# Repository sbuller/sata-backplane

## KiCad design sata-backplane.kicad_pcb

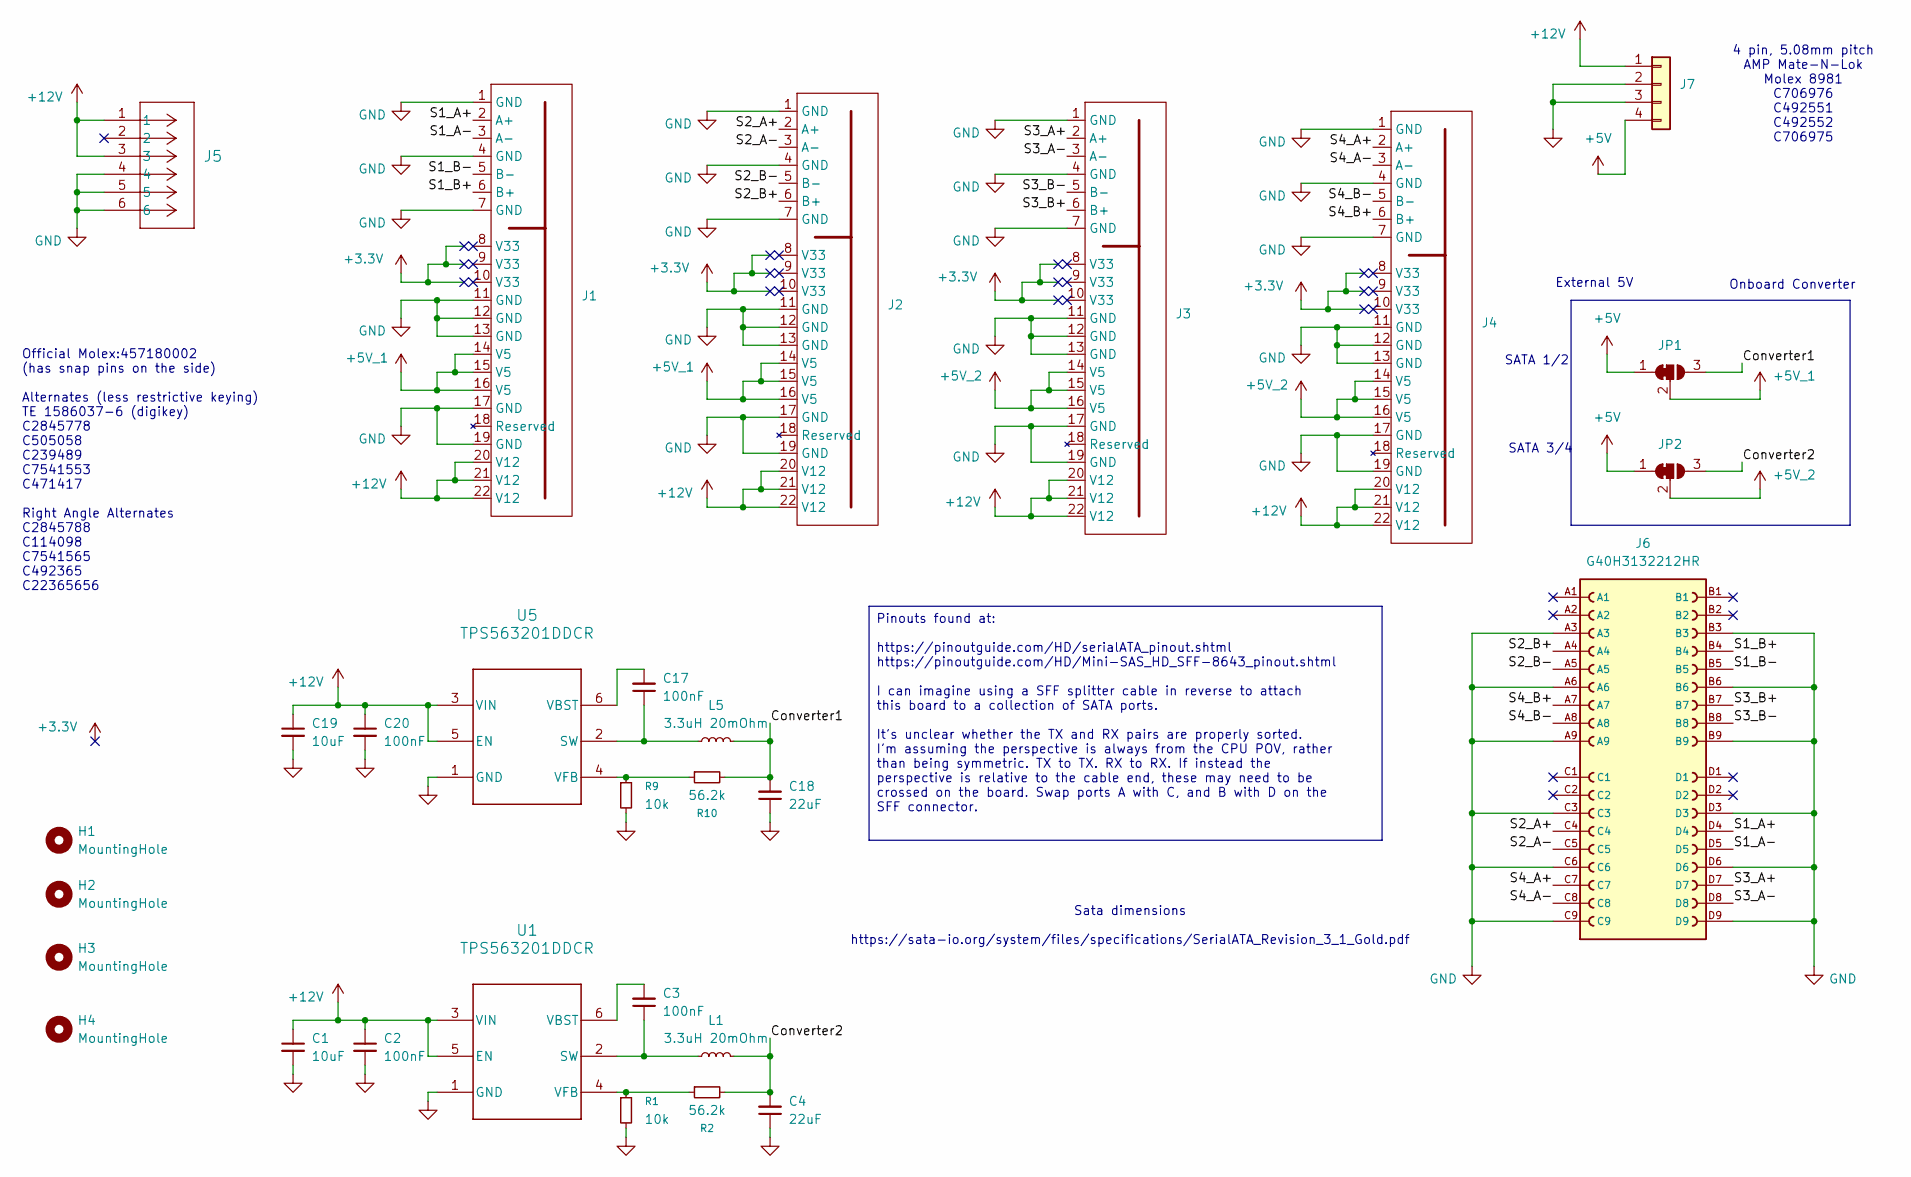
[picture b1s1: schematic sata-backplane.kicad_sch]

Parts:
C1, C19: 10uF; C_0603_1608Metric_Pad1.08x0.95mm_HandSolder
C2, C3, C17, C20: 100nF; C_0603_1608Metric_Pad1.08x0.95mm_HandSolder
C4, C18: 22uF; C_0603_1608Metric_Pad1.08x0.95mm_HandSolder
H1, H2, H3, H4: MountingHole; MountingHole_3.2mm_M3_Pad
J1, J2, J3, J4: Sata+15P; LCSC C19193804
J5: 457180002; CONN_SD-45718-001_MOL
J6: G40H3132212HR; AMPHENOL_G40H3132212HR; PARTREV C
J7: Conn_01x04; 350211-1_TYC
JP1, JP2: SolderJumper_3_Open; SolderJumper-3_P1.3mm_Bridged12_RoundedPad1.0x1.5mm
L1, L5: 3.3uH 20mOhm; SL0420; LCSC C22463807
R1, R9: 10k; R_0603_1608Metric_Pad0.98x0.95mm_HandSolder
R2, R10: 56.2k; R_0603_1608Metric_Pad0.98x0.95mm_HandSolder
U1: TPS563201DDCR; SOT-23-6_Handsoldering
U5: TPS563201DDCR; SOT-23-6_Handsoldering; LCSC C116592

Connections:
+5V: J7.4, JP1.1 (A), JP2.1 (A)
+5V_1: J1.14 (V5), J1.15 (V5), J1.16 (V5), J2.14 (V5), J2.15 (V5), J2.16 (V5), JP1.2 (C)
+5V_2: J3.14 (V5), J3.15 (V5), J3.16 (V5), J4.14 (V5), J4.15 (V5), J4.16 (V5), JP2.2 (C)
+12V: C1.1, C2.1, C19.1, C20.1, J1.20 (V12), J1.21 (V12), J1.22 (V12), J2.20 (V12), J2.21 (V12), J2.22 (V12), J3.20 (V12), J3.21 (V12), J3.22 (V12), J4.20 (V12), J4.21 (V12), J4.22 (V12), J5.1, J5.3, J7.1, U1.3 (VIN), U1.5 (EN), U5.3 (VIN), U5.5 (EN)
/Converter1: C18.2, JP1.3 (B), L5.2, R10.2
/Converter2: C4.2, JP2.3 (B), L1.2, R2.2
/S1_A+: J1.2 (A+), J6.D4
/S1_A-: J1.3 (A-), J6.D5
/S1_B+: J1.6 (B+), J6.B4
/S1_B-: J1.5 (B-), J6.B5
/S2_A+: J2.2 (A+), J6.C4
/S2_A-: J2.3 (A-), J6.C5
/S2_B+: J2.6 (B+), J6.A4
/S2_B-: J2.5 (B-), J6.A5
/S3_A+: J3.2 (A+), J6.D7
/S3_A-: J3.3 (A-), J6.D8
/S3_B+: J3.6 (B+), J6.B7
/S3_B-: J3.5 (B-), J6.B8
/S4_A+: J4.2 (A+), J6.C7
/S4_A-: J4.3 (A-), J6.C8
/S4_B+: J4.6 (B+), J6.A7
/S4_B-: J4.5 (B-), J6.A8
GND: C1.2, C2.2, C4.1, C18.1, C19.2, C20.2, J1.1 (GND), J1.4 (GND), J1.7 (GND), J1.11 (GND), J1.12 (GND), J1.13 (GND), J1.17 (GND), J1.19 (GND), J2.1 (GND), J2.4 (GND), J2.7 (GND), J2.11 (GND), J2.12 (GND), J2.13 (GND), J2.17 (GND), J2.19 (GND), J3.1 (GND), J3.4 (GND), J3.7 (GND), J3.11 (GND), J3.12 (GND), J3.13 (GND), J3.17 (GND), J3.19 (GND), J4.1 (GND), J4.4 (GND), J4.7 (GND), J4.11 (GND), J4.12 (GND), J4.13 (GND), J4.17 (GND), J4.19 (GND), J5.4, J5.5, J5.6, J6.A3, J6.A6, J6.A9, J6.B3, J6.B6, J6.B9, J6.C3, J6.C6, J6.C9, J6.D3, J6.D6, J6.D9, J7.2, J7.3, R1.2, R9.2, U1.1 (GND), U5.1 (GND)
unnamed: C3.1, L1.1, U1.2 (SW)
unnamed: C3.2, U1.6 (VBST)
unnamed: R1.1, R2.1, U1.4 (VFB)
unnamed: C17.1, L5.1, U5.2 (SW)
unnamed: C17.2, U5.6 (VBST)
unnamed: R9.1, R10.1, U5.4 (VFB)

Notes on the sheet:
SATA 1/2
Official Molex:457180002 (has snap pins on the side) Alternates (less restrictive keying) TE 1586037-6 (digikey) C2845778 C505058 C239489 C7541553 C471417 Right Angle Alternates C2845788 C114098 C7541565 C492365 C22365656
SATA 3/4
Sata dimensions https://sata-io.org/system/files/specifications/SerialATA_Revision_3_1_Gold.pdf
4 pin, 5.08mm pitch AMP Mate-N-Lok Molex 8981 C706976 C492551 C492552 C706975
Onboard Converter
External 5V
Pinouts found at: https://pinoutguide.com/HD/serialATA_pinout.shtml https://pinoutguide.com/HD/Mini-SAS_HD_SFF-8643_pinout.shtml I can imagine using a SFF splitter cable in reverse to attach this board to a collection of SATA ports. It's unclear whether the TX and RX pairs are properly sorted. I'm 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

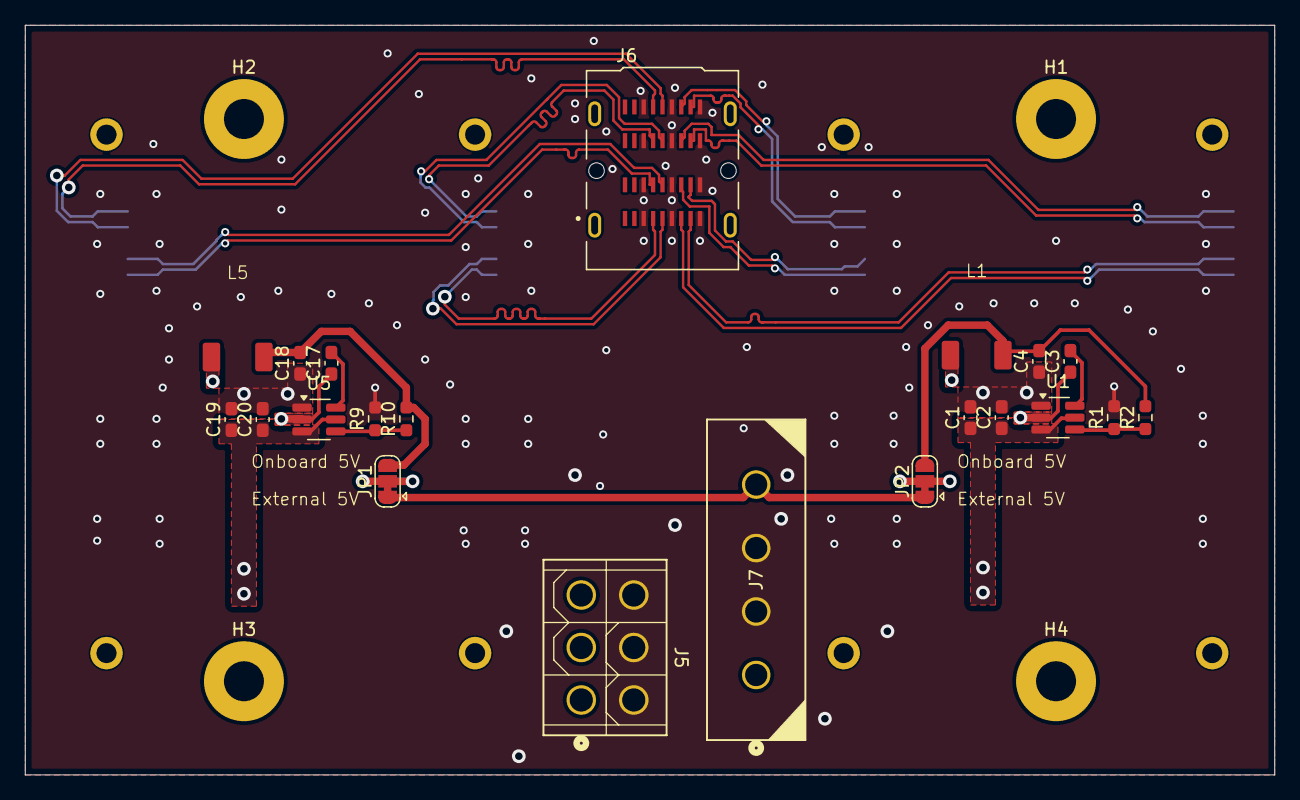
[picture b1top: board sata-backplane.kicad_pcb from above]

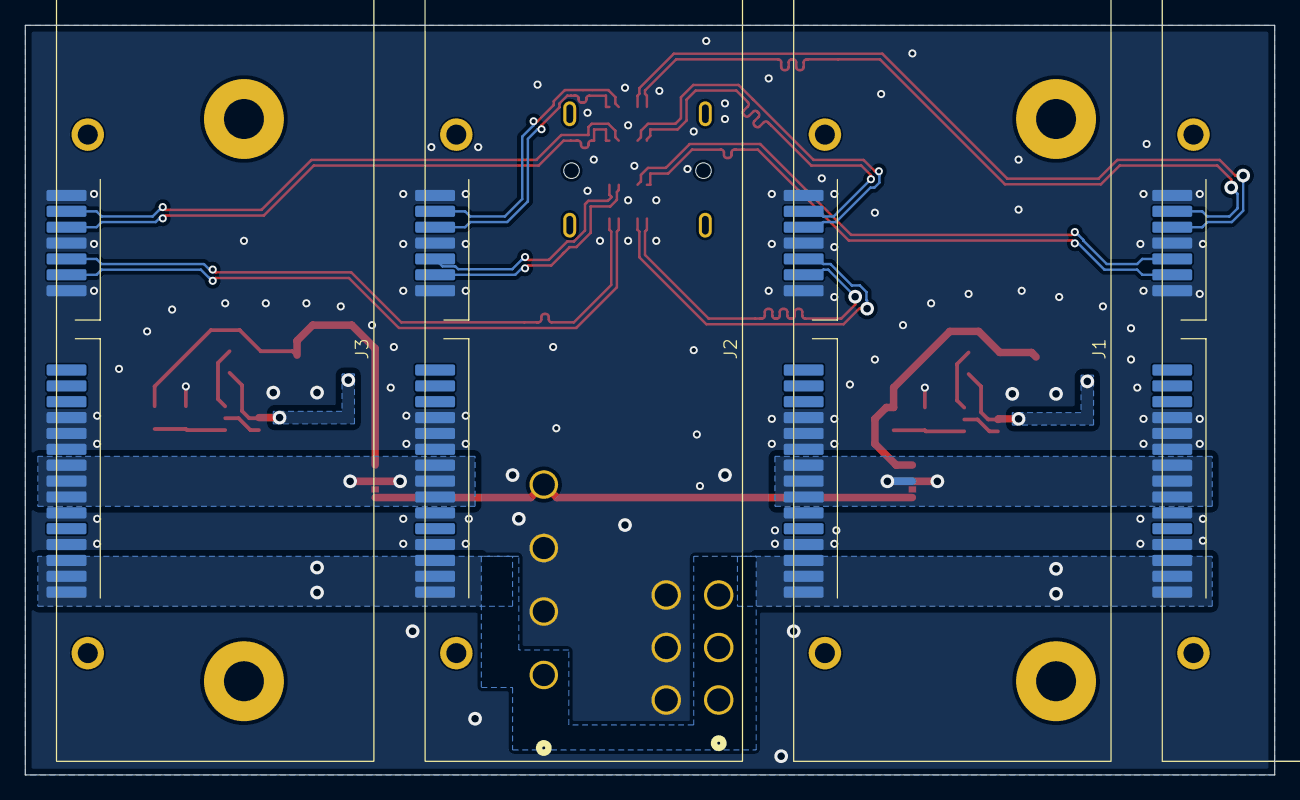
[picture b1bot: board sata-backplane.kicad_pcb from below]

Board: 2 copper layers, 100.0 x 60.0 mm, 29 parts (4 on the bottom side), 29 nets.

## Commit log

2025-05-24 Sketch of a sata backplane
2025-05-25 Switch to two 3A converters from 4 2A
2025-05-25 Rough layout
2025-05-25 Wire up power
2025-05-25 Routed
2025-05-25 Add Molex HD power connector
